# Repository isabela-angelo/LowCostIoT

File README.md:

# LowCostIoT
Hardware, Embedded software and Android App for Internet of Things, with low cost components.

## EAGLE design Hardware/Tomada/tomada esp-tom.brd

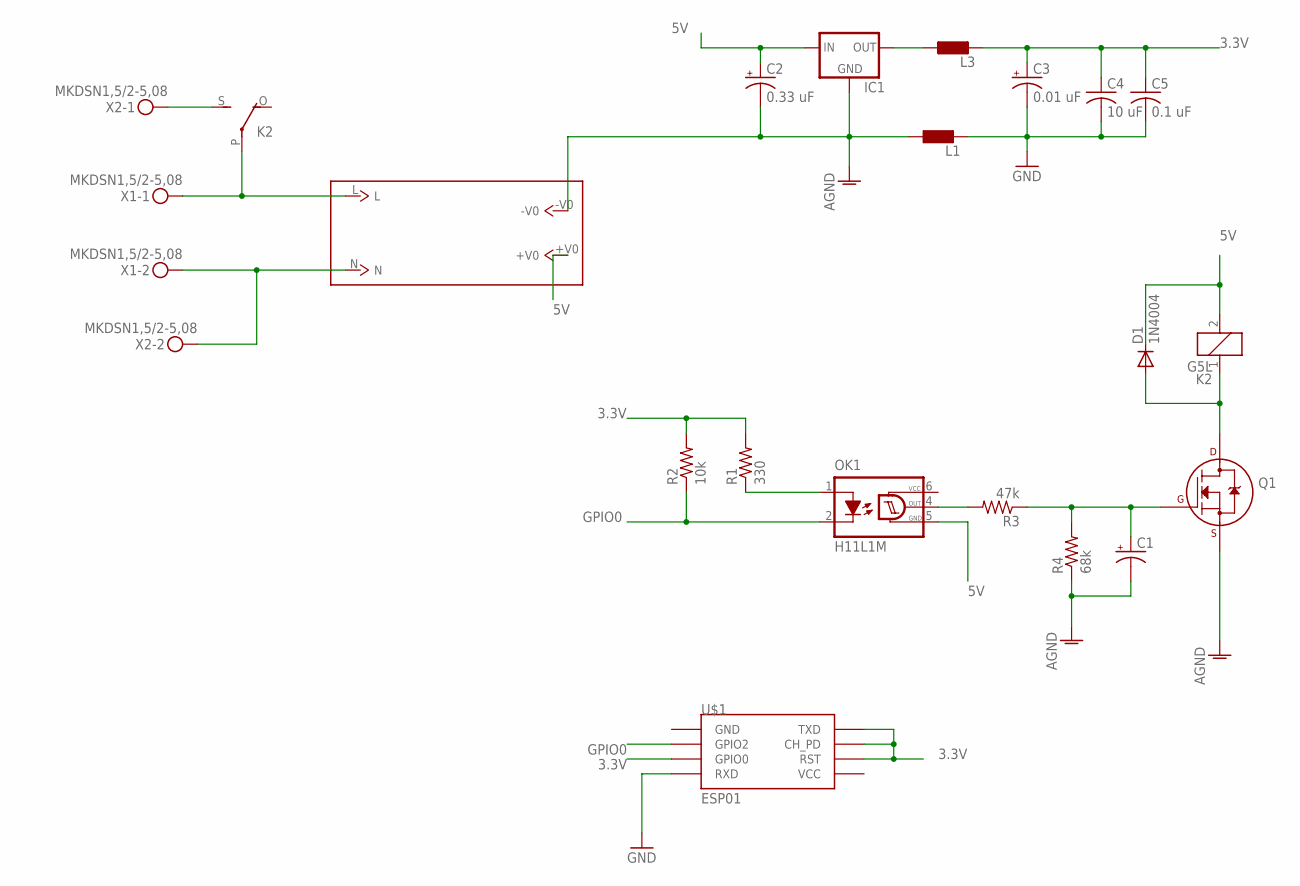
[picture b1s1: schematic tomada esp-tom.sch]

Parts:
C1: CPOL-USE2-5; E2-5
C2: 0.33 uF; E2-5
C3: 0.01 uF; E2-5
C4: 10 uF; C025-024X044
C5: 0.1 uF; C025-024X044
D1: 1N4004; DO41-10
IC1: 78LXX
K2: G5L; G5LE
L1, L3: L0207/10; 0207/10
OK1: H11L1M; DIL06
Q1: 2N7000_TO92; TO-92
R1: 330; 0204/7
R2: 10k; 0204/7
R3: 47k; 0204/7
R4: 68k; 0204/7
U$1: ESP01
U$2: NA03-T2S05
X1, X2: MKDSN1,5/2-5,08

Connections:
3.3V: C3.+, C4.1, C5.1, L3.2, R1.2, R2.2, U$1.CH_PD, U$1.GPIO0, U$1.RST, U$1.TX (TXD)
5V: C2.+, D1.C, IC1.IN, K2.2, OK1.5 (GND), U$2.+V0
AGND: C1.-, C2.-, IC1.GND, L1.1, Q1.1 (S), R4.1, U$2.-V0
GND: C3.-, C4.2, C5.2, L1.2, U$1.RX (RXD)
GPIO0: OK1.2 (C), R2.1, U$1.GPIO2
unnamed: OK1.1 (A), R1.1
unnamed: C1.+, Q1.2 (G), R3.1, R4.2
unnamed: OK1.4 (OUT), R3.2
unnamed: D1.A, K2.1, Q1.3 (D)
unnamed: K2.S, X2.1
unnamed: K2.P, U$2.L, X1.1
unnamed: U$2.N, X1.2, X2.2
unnamed: IC1.OUT, L3.1
VCC: OK1.6 (VCC)

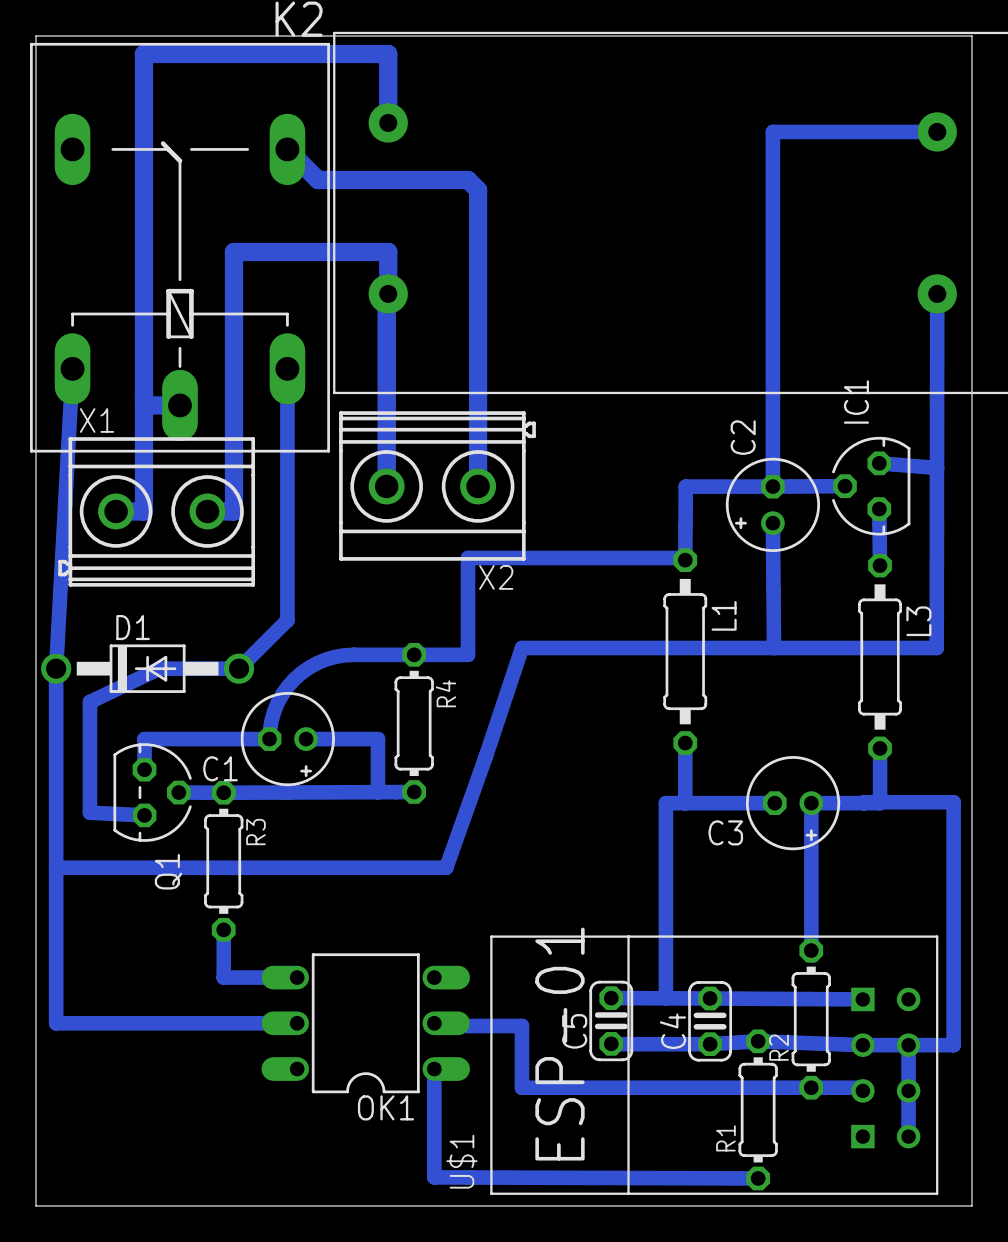
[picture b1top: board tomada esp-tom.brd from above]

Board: 2 copper layers, 52.0 x 65.0 mm, 20 parts (0 on the bottom side), 13 nets.

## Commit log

2015-10-29 Primeira carga de arquivos do hardware
    Esquemático e pcb tanto da tomada quanto do interruptor
2015-10-29 Upload dos arquivos gerber
    Upload dos arquivos gerber dos 2 projetos em formato zip
2015-11-08 aplicativo do usado no TOM
